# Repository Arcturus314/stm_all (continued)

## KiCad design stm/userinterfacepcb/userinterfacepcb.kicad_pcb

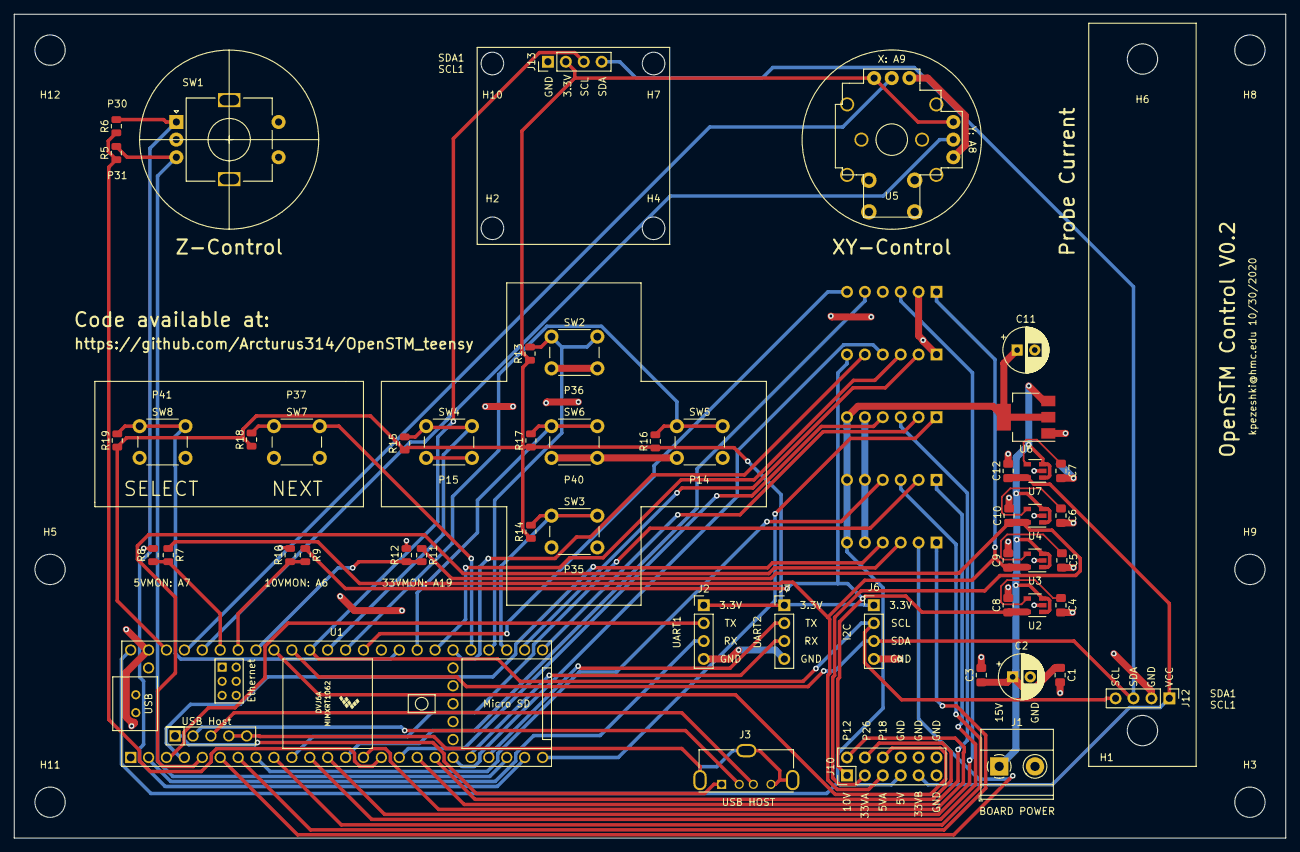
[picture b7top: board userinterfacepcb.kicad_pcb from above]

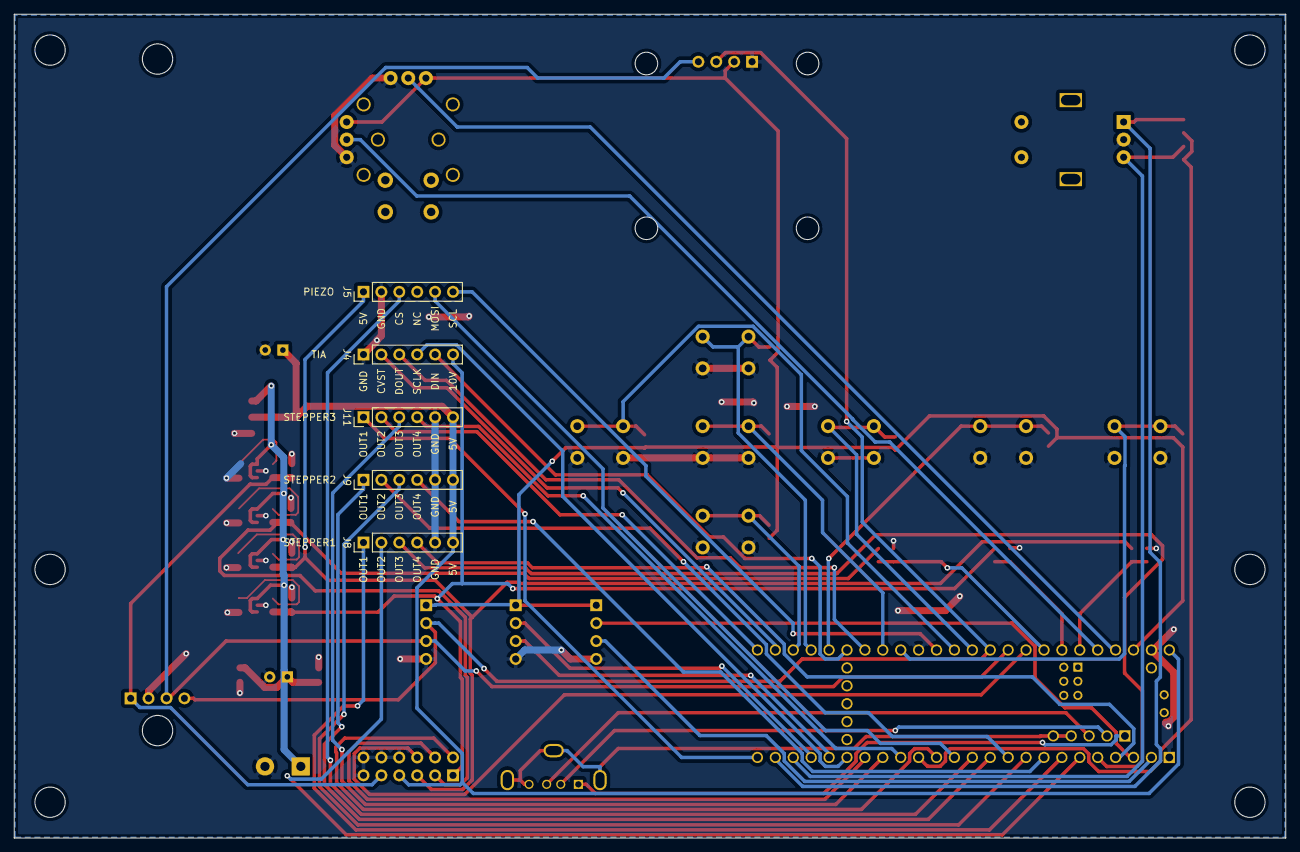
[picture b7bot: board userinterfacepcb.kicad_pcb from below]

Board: 2 copper layers, 180.3 x 116.8 mm, 67 parts (5 on the bottom side), 59 nets.

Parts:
C1, C3: 1uF; C_0805_2012Metric_Pad1.15x1.40mm_HandSolder
C2: 47uF; CP_Radial_D6.3mm_P2.50mm
C4, C5, C6, C7: 10nF; C_0805_2012Metric_Pad1.15x1.40mm_HandSolder
C8, C9, C10, C12: 2.2uF; C_0805_2012Metric_Pad1.15x1.40mm_HandSolder
C11: 10uF; CP_Radial_D6.3mm_P2.50mm
H1, H3, H5, H6, H8, H9, H11, H12: MountingHole; MountingHole_4.3mm_M4
H2, H4, H7, H10: MountingHole; MountingHole_3.2mm_M3
J1: Conn_01x02_Male; TerminalBlock_Phoenix_MKDS-1,5-2-5.08_1x02_P5.08mm_Horizont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
J2, J6, J7: Conn_01x04_Male; PinHeader_1x04_P2.54mm_Vertical
J3: USB_A; USB_A_Molex_105057_Vertical
J4, J5, J8, J9, J11: Conn_01x06_Male; PinHeader_1x06_P2.54mm_Vertical
J10: Conn_02x06_Odd_Even; PinHeader_2x06_P2.54mm_Vertical
J12, J13: Conn_01x04_Female; PinHeader_1x04_P2.54mm_Vertical
R5, R6, R8, R10, R11, R12, R13, R14, R15, R16, R17, R18, R19: 10k; R_0805_2012Metric
R7: 20k; R_0805_2012Metric
R9: 47k; R_0805_2012Metric
SW1: Rotary_Encoder; RotaryEncoder_Alps_EC11E-Switch_Vertical_H20mm
SW2, SW3, SW4, SW5, SW6, SW7, SW8: SW_Push; SW_PUSH_6mm_H8mm
U1: Teensy4.1; Teensy41
U2: LP2985-10.0; SOT-23-5
U3: LP2985-5.0; SOT-23-5
U4, U7: LP2985-3.3; SOT-23-5
U5: RKJXV1224005
U6: NCP1117-5.0_SOT223; SOT-223-3_TabPin2

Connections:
+3.3VA: C10.1, J10.3, R11.1, U4.5
+3V3: J2.1, J6.1, J7.1, J13.2, R13.1, R14.1, R15.1, R16.1, R17.1, R18.1, R19.1, U1.46, U5.3, U5.6
+5V: C11.1, J8.6, J9.6, J10.7, J11.6, U1.48, U6.2
+5VA: C9.1, J5.1, J10.5, R7.1, U3.5
+10V: C8.1, J4.6, J10.1, R9.1, U2.5
+15V: C1.1, C2.1, C3.1, J1.1, U2.1, U2.3, U3.1, U3.3, U4.1, U4.3, U6.3, U7.1, U7.3
/5VMON: R7.2, R8.1, U1.43
/10VMON: R9.2, R10.1, U1.42
/33VBAR: C12.1, J10.9, J12.1, U7.5
/33VMON: R11.2, R12.1, U1.41
/DISPLAYSCL: J6.2, J12.4, J13.3, U1.38
/DISPLAYSDA: J6.3, J12.3, J13.4, U1.39
/DOWN: R14.2, SW3.1, U1.27
/ENCODERSEL: R19.2, SW8.1, U1.33
/IO1: J10.2, U1.14
/IO2: J10.4, U1.18
/IO3: J10.6, U1.40
/JOYAX1: U1.45, U5.5
/JOYAX2: U1.44, U5.2
/LEFT: R15.2, SW4.1, U1.37
/NEXT: R18.2, SW7.1, U1.29
/PIEZOCLK: J5.6, U1.35
/PIEZOCS: J5.3, U1.12
/PIEZOMOSI: J5.5, U1.13
/RIGHT: R16.2, SW5.1, U1.36
/RX1OUT: J2.3, U1.2
/RX2OUT: J7.3, U1.20
/SELECT: R17.2, SW6.1, U1.32
/STEPPER1_1: J8.1, U1.7
/STEPPER1_2: J8.2, U1.6
/STEPPER1_3: J8.3, U1.5
/STEPPER1_4: J8.4, U1.4
/STEPPER2_1: J9.1, U1.11
/STEPPER2_2: J9.2, U1.10
/STEPPER2_3: J9.3, U1.9
/STEPPER2_4: J9.4, U1.8
/STEPPER3_1: J11.1, U1.24
/STEPPER3_2: J11.2, U1.25
/STEPPER3_3: J11.3, U1.17
/STEPPER3_4: J11.4, U1.16
/TIA_CONVST: J4.2, U1.26
/TIA_DIN: J4.5, U1.30
/TIA_DOUT: J4.3, U1.31
/TIA_SCLK: J4.4, U1.19
/TX1OUT: J2.2, U1.3
/TX2OUT: J7.2, U1.21
/UP: R13.2, SW2.1, U1.28
GND: C1.2, C2.2, C3.2, C4.2, C5.2, C6.2, C7.2, C8.2, C9.2, C10.2, C11.2, C12.2, J1.2, J2.4, J4.1, J5.2, J6.4, J7.4, J8.5, J9.5, J10.8, J10.10, J10.11, J10.12, J11.5, J12.2, J13.1, R8.2, R10.2, R12.2, SW1.C, SW2.2, SW3.2, SW4.2, SW5.2, SW6.2, SW7.2, SW8.2, U1.1, U1.34, U1.47, U2.2, U3.2, U4.2, U5.1, U5.4, U6.1, U7.2
unnamed: C4.1, U2.4
unnamed: C5.1, U3.4
unnamed: C6.1, U4.4
unnamed: C7.1, U7.4
unnamed: J3.1, U1.55
unnamed: J3.2, U1.56
unnamed: J3.3, U1.57
unnamed: J3.4, J3.5, U1.58, U1.59
unnamed: R5.1, R6.1, U1.15
unnamed: R5.2, SW1.B, U1.22
unnamed: R6.2, SW1.A, U1.23

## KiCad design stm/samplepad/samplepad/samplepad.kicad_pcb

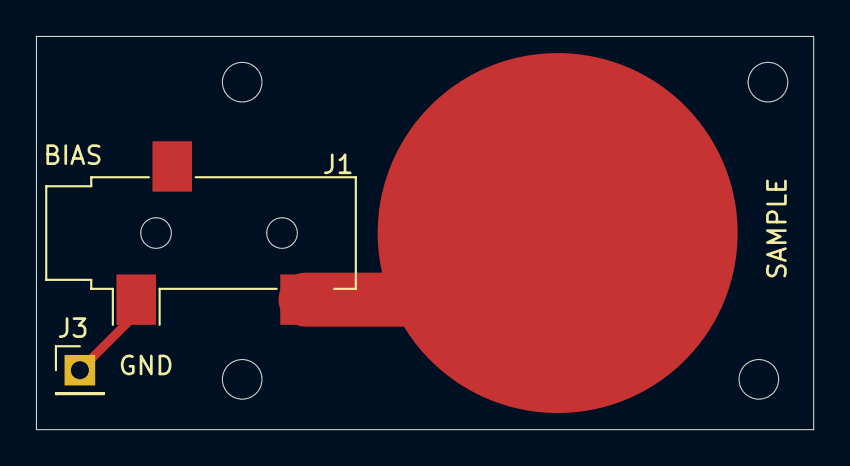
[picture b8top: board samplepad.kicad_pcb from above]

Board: 2 copper layers, 43.2 x 21.8 mm, 7 parts (0 on the bottom side), 2 nets.

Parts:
H1, H2, H3, H4: MountingHole; MountingHole_2.2mm_M2
J1: AudioJack2; Jack_3.5mm_CUI_SJ-3523-SMT_Horizontal
J2: Conn_01x01_Female; mountingpad
J3: Conn_01x01_Female; PinHeader_1x01_P2.54mm_Vertical

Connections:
unnamed: J1.S, J3.1
unnamed: J1.T, J2.1

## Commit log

2021-03-22 added current state of project
